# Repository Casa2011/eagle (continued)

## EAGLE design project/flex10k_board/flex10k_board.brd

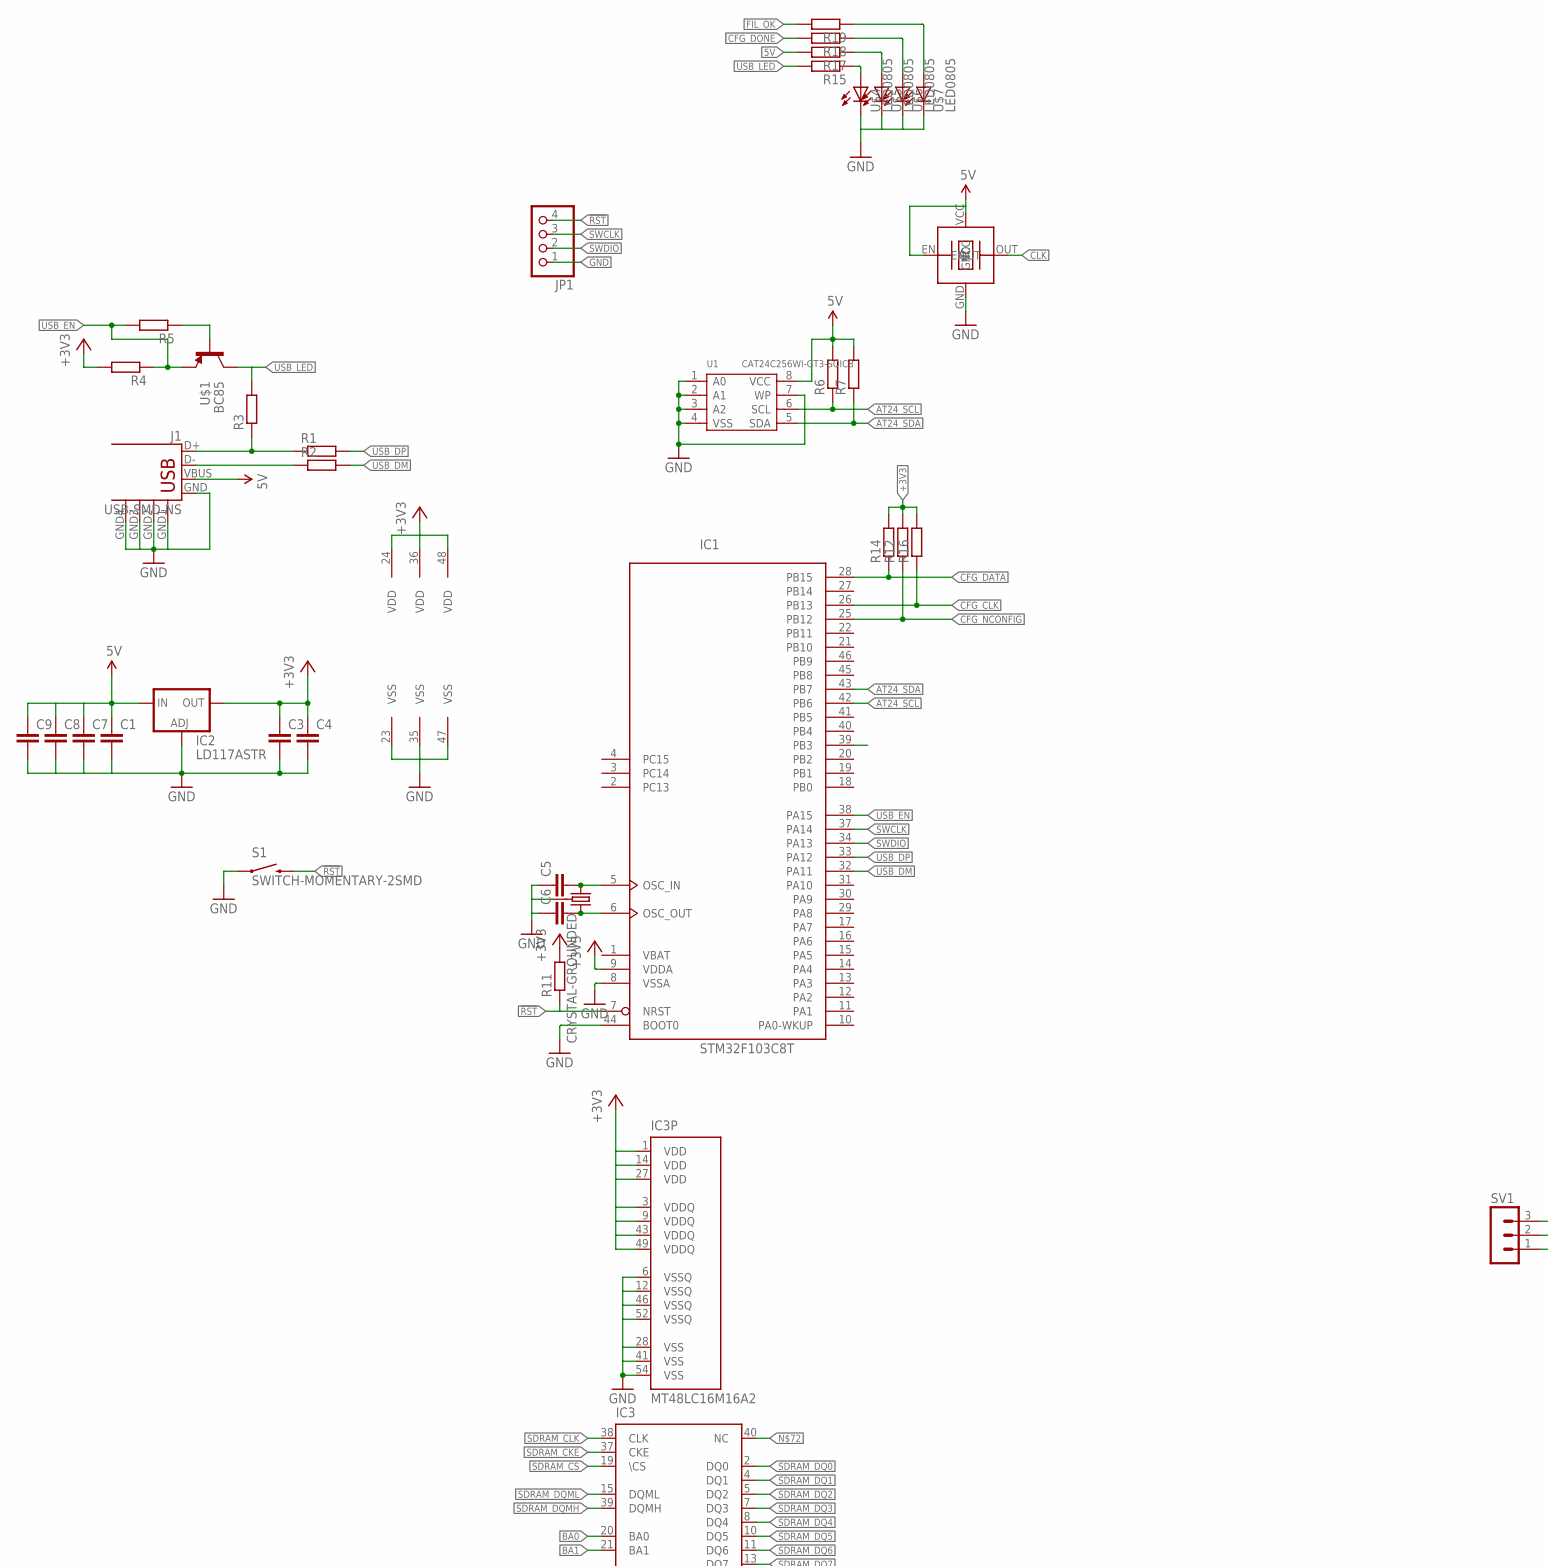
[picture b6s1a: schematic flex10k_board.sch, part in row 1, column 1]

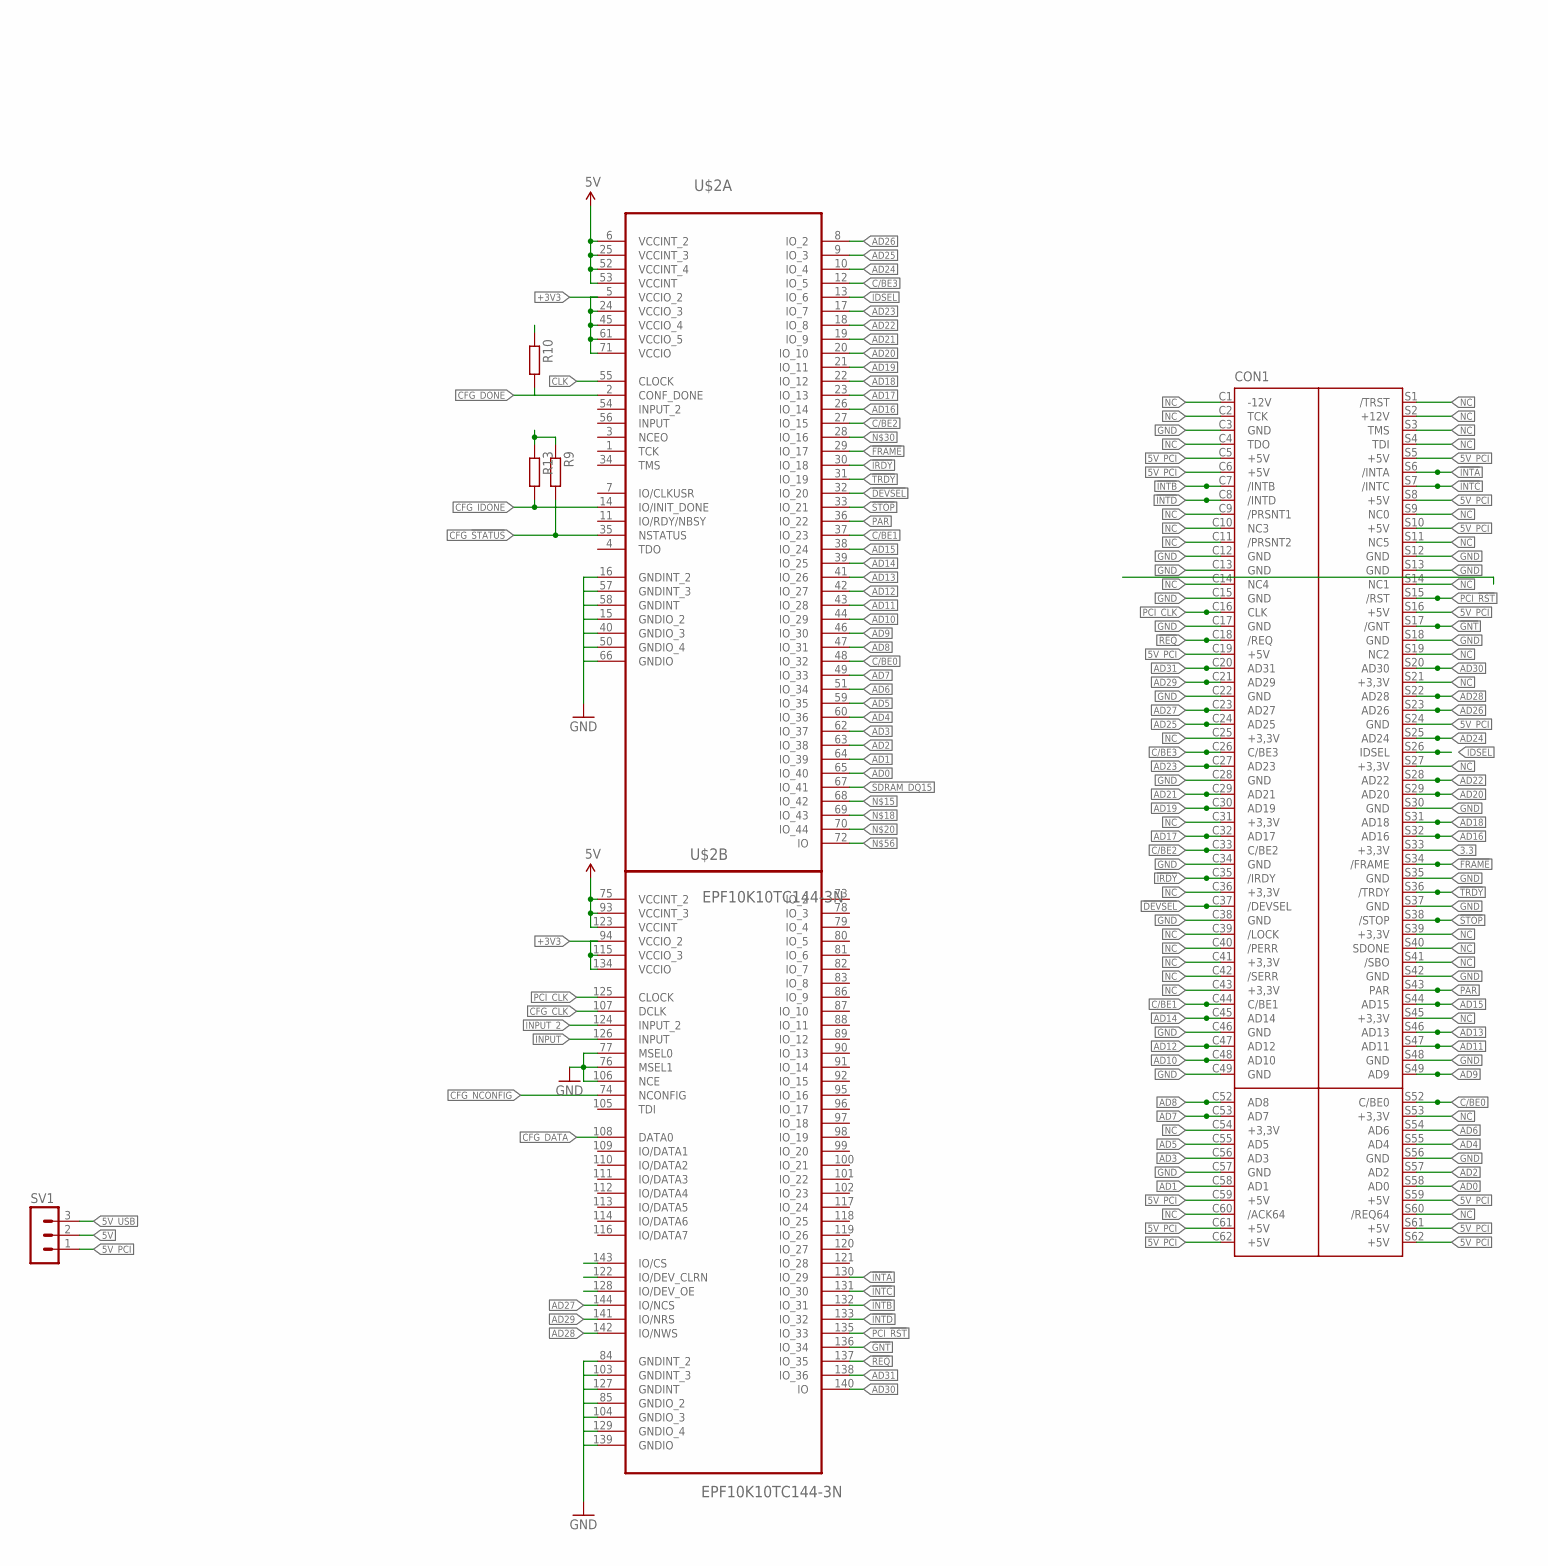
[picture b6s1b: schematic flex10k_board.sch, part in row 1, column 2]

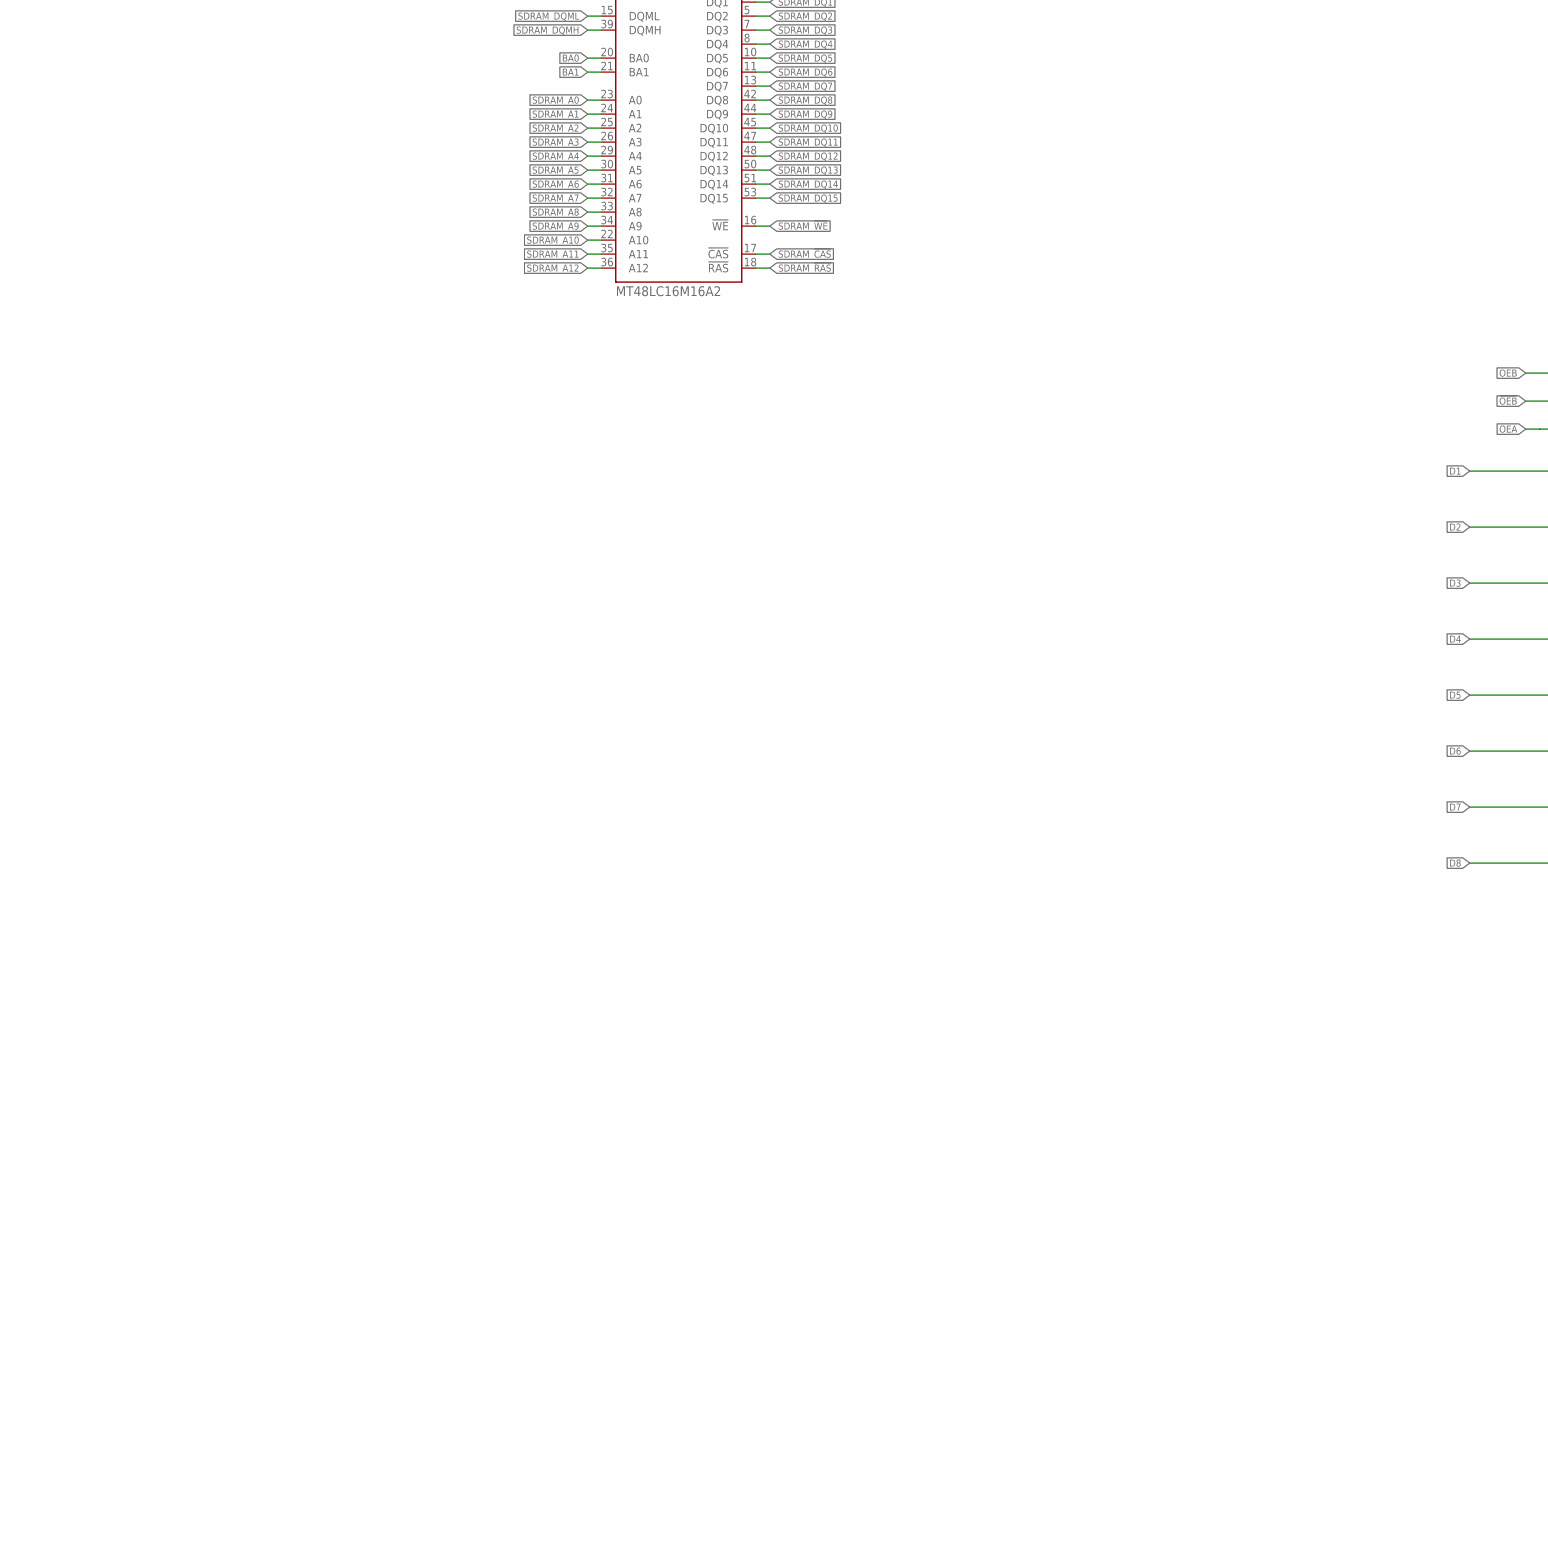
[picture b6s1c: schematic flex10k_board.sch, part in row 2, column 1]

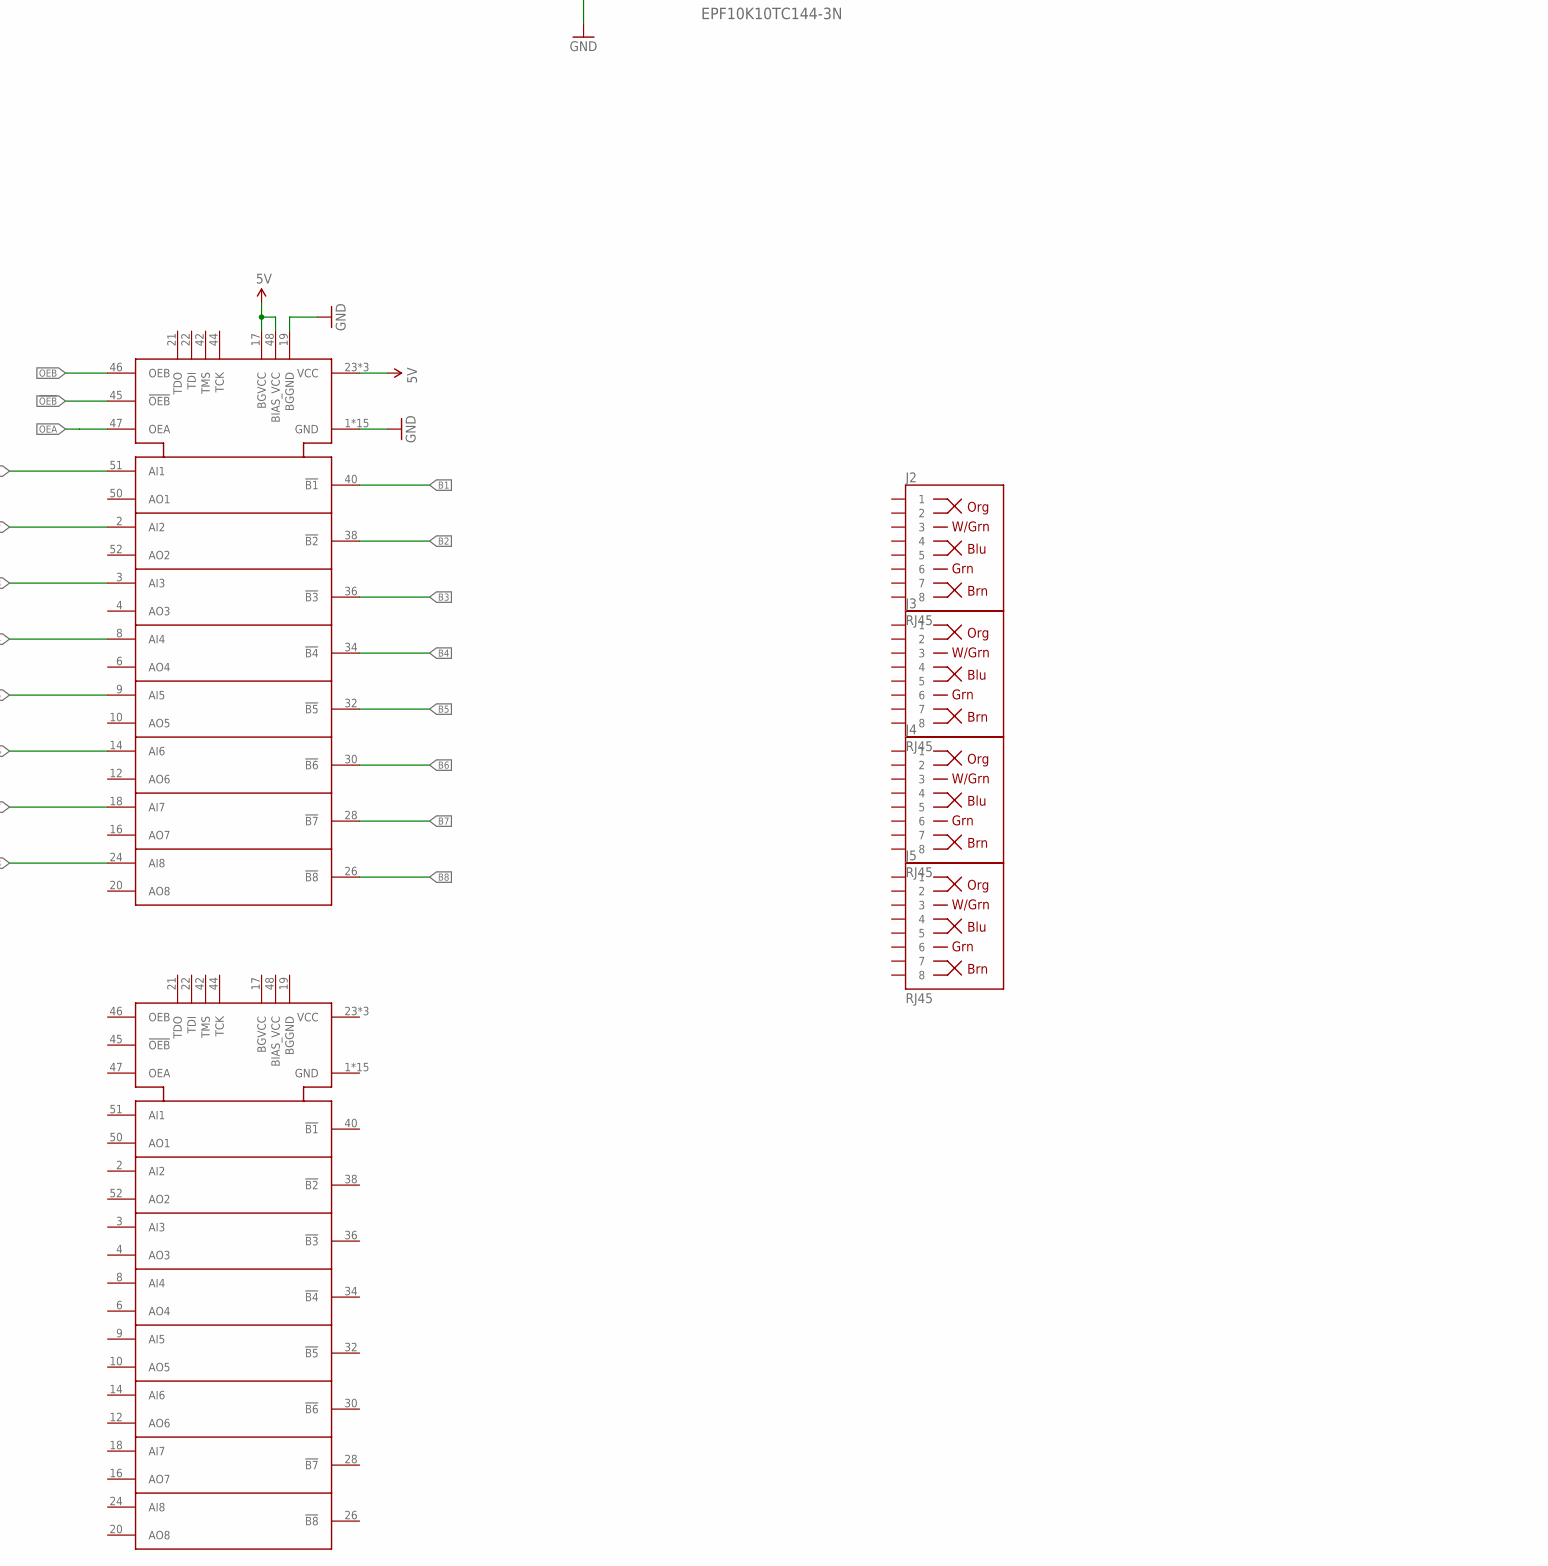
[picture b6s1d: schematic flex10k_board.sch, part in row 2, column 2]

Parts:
C1, C3, C4, C7, C8, C9: CC0805; C0805
C5, C6: CC0603; C0603
CON1: PCI_CON; PCI_BRDL
IC1: STM32F103C8T; LQFP48
IC2: LD117ASTR; SOT223
IC3: MT48LC16M16A2; TSOP54-400
J1: USB-SMD-NS; USB-MINIB-NOSTOP
J2, J3, J4, J5: RJ45; RJ45-8
JP1: PINHD-1X4; 1X04
R1, R2, R3, R4, R5, R6, R7, R9, R10, R11, R12, R13, R14, R15, R16, R17, R18, R19: R0603; 0603
S1: SWITCH-MOMENTARY-2SMD; TACTILE-SWITCH-SMD
SV1: MA03-1
U1: CAT24C256WI-GT3-SOIC8; SOIC8-1.27-5X4MM
U$1: BC85; SOT23
U$2: EPF10K10TC144-3N; QFP50P2200X2200X160-144N
U$3: TXC-BA; 7X5
U$4, U$5, U$6, U$7: LED0805; 0805-LED
U$8: CRYSTAL-GROUNDED; CRYSTAL-SMD-5X3
U$9, U$10: SN74FB2050; TQFP-10X10-52

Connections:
3.3: CON1.S33 (+3,3V)
5V: C1.1, C7.1, C8.1, C9.1, IC2.3 (IN), R6.2, R7.2, R17.2, SV1.2, U1.8 (VCC), U$2.6 (VCCINT_2), U$2.25 (VCCINT_3), U$2.52 (VCCINT_4), U$2.53 (VCCINT), U$2.75 (VCCINT_2), U$2.93 (VCCINT_3), U$2.123 (VCCINT), U$3.EN, U$3.VCC, U$10.17 (BGVCC), U$10.23 (VCC), U$10.43 (VCC), U$10.48 (BIAS_VCC), U$10.49 (VCC)
5V_PCI: CON1.C5 (+5V), CON1.C6 (+5V), CON1.C19 (+5V), CON1.C59 (+5V), CON1.C61 (+5V), CON1.C62 (+5V), CON1.S5 (+5V), CON1.S8 (+5V), CON1.S10 (+5V), CON1.S16 (+5V), CON1.S24 (GND), CON1.S59 (+5V), CON1.S61 (+5V), CON1.S62 (+5V), SV1.1
5V_USB: J1.VBUS, SV1.3
!DEVSEL: CON1.C37 (/DEVSEL), U$2.32 (IO_20)
!FRAME: CON1.S34 (/FRAME), U$2.29 (IO_17)
!GNT: CON1.S17 (/GNT), U$2.136 (IO_34)
!INTA: CON1.S6 (/INTA), U$2.130 (IO_29)
!INTB: CON1.C7 (/INTB), U$2.132 (IO_31)
!INTC: CON1.S7 (/INTC), U$2.131 (IO_30)
!INTD: CON1.C8 (/INTD), U$2.133 (IO_32)
!IRDY: CON1.C35 (/IRDY), U$2.30 (IO_18)
!OEB: U$10.45 (!OEB)
!REQ: CON1.C18 (/REQ), U$2.137 (IO_35)
!RST: IC1.7 (NRST), JP1.4, R11.1, S1.3 (2)
!STOP: CON1.S38 (/STOP), U$2.33 (IO_21)
!TRDY: CON1.S36 (/TRDY), U$2.31 (IO_19)
+3V3: C3.1, C4.1, IC1.9 (VDDA), IC1.24 (VDD), IC1.36 (VDD), IC1.48 (VDD), IC2.4 (OUT), IC3.1 (VDD), IC3.3 (VDDQ), IC3.9 (VDDQ), IC3.14 (VDD), IC3.27 (VDD), IC3.43 (VDDQ), IC3.49 (VDDQ), R4.2, R9.1, R10.1, R11.2, R12.2, R13.1, R14.2, R16.2, U$2.5 (VCCIO_2), U$2.24 (VCCIO_3), U$2.45 (VCCIO_4), U$2.61 (VCCIO_5), U$2.71 (VCCIO), U$2.94 (VCCIO_2), U$2.115 (VCCIO_3), U$2.134 (VCCIO)
AD0: CON1.S58 (AD0), U$2.65 (IO_40)
AD1: CON1.C58 (AD1), U$2.64 (IO_39)
AD2: CON1.S57 (AD2), U$2.63 (IO_38)
AD3: CON1.C56 (AD3), U$2.62 (IO_37)
AD4: CON1.S55 (AD4), U$2.60 (IO_36)
AD5: CON1.C55 (AD5), U$2.59 (IO_35)
AD6: CON1.S54 (AD6), U$2.51 (IO_34)
AD7: CON1.C53 (AD7), U$2.49 (IO_33)
AD8: CON1.C52 (AD8), U$2.47 (IO_31)
AD9: CON1.S49 (AD9), U$2.46 (IO_30)
AD10: CON1.C48 (AD10), U$2.44 (IO_29)
AD11: CON1.S47 (AD11), U$2.43 (IO_28)
AD12: CON1.C47 (AD12), U$2.42 (IO_27)
AD13: CON1.S46 (AD13), U$2.41 (IO_26)
AD14: CON1.C45 (AD14), U$2.39 (IO_25)
AD15: CON1.S44 (AD15), U$2.38 (IO_24)
AD16: CON1.S32 (AD16), U$2.26 (IO_14)
AD17: CON1.C32 (AD17), U$2.23 (IO_13)
AD18: CON1.S31 (AD18), U$2.22 (IO_12)
AD19: CON1.C30 (AD19), U$2.21 (IO_11)
AD20: CON1.S29 (AD20), U$2.20 (IO_10)
AD21: CON1.C29 (AD21), U$2.19 (IO_9)
AD22: CON1.S28 (AD22), U$2.18 (IO_8)
AD23: CON1.C27 (AD23), U$2.17 (IO_7)
AD24: CON1.S25 (AD24), U$2.10 (IO_4)
AD25: CON1.C24 (AD25), U$2.9 (IO_3)
AD26: CON1.S23 (AD26), U$2.8 (IO_2)
AD27: CON1.C23 (AD27), U$2.144 (IO/NCS)
AD28: CON1.S22 (AD28), U$2.142 (IO/NWS)
AD29: CON1.C21 (AD29), U$2.141 (IO/NRS)
AD30: CON1.S20 (AD30), U$2.140 (IO)
AD31: CON1.C20 (AD31), U$2.138 (IO_36)
AT24_SCL: IC1.42 (PB6), R6.1, U1.6 (SCL)
AT24_SDA: IC1.43 (PB7), R7.1, U1.5 (SDA)
B1: U$10.40 (!B1)
B2: U$10.38 (!B2)
B3: U$10.36 (!B3)
B4: U$10.34 (!B4)
B5: U$10.32 (!B5)
B6: U$10.30 (!B6)
B7: U$10.28 (!B7)
B8: U$10.26 (!B8)
BA0: IC3.20 (BA0)
BA1: IC3.21 (BA1)
C/BE0: CON1.S52 (C/BE0), U$2.48 (IO_32)
C/BE1: CON1.C44 (C/BE1), U$2.37 (IO_23)
C/BE2: CON1.C33 (C/BE2), U$2.27 (IO_15)
C/BE3: CON1.C26 (C/BE3), U$2.12 (IO_5)
CFG_!STATUS: R9.2, U$2.35 (NSTATUS)
CFG_CLK: IC1.26 (PB13), R16.1, U$2.107 (DCLK)
CFG_DATA: IC1.28 (PB15), R14.1, U$2.108 (DATA0)
CFG_DONE: R10.2, R18.2, U$2.2 (CONF_DONE)
CFG_IDONE: R13.2, U$2.14 (IO/INIT_DONE)
CFG_NCONFIG: IC1.25 (PB12), R12.1, U$2.74 (NCONFIG)
CLK: U$2.55 (CLOCK), U$3.OUT
D1: U$10.51 (AI1)
D2: U$10.2 (AI2)
D3: U$10.3 (AI3)
D4: U$10.8 (AI4)
D5: U$10.9 (AI5)
D6: U$10.14 (AI6)
D7: U$10.18 (AI7)
D8: U$10.24 (AI8)
FIL_OK: IC1.39 (PB3), R19.2
GND: C1.2, C3.2, C4.2, C5.1, C6.1, C7.2, C8.2, C9.2, CON1.C3 (GND), CON1.C12 (GND), CON1.C13 (GND), CON1.C15 (GND), CON1.C17 (GND), CON1.C22 (GND), CON1.C28 (GND), CON1.C34 (GND), CON1.C38 (GND), CON1.C46 (GND), CON1.C49 (GND), CON1.C57 (GND), CON1.S12 (GND), CON1.S13 (GND), CON1.S18 (GND), CON1.S30 (GND), CON1.S35 (GND), CON1.S37 (GND), CON1.S42 (GND), CON1.S48 (GND), CON1.S56 (GND), IC1.8 (VSSA), IC1.23 (VSS), IC1.35 (VSS), IC1.44 (BOOT0), IC1.47 (VSS), IC2.1 (ADJ), IC3.6 (VSSQ), IC3.12 (VSSQ), IC3.28 (VSS), IC3.41 (VSS), IC3.46 (VSSQ), IC3.52 (VSSQ), IC3.54 (VSS), J1.GND, J1.GND1 (GND), J1.GND2 (GND), J1.GND3 (GND), J1.GND4 (GND), JP1.1, S1.1, U1.1 (A0), U1.2 (A1), U1.3 (A2), U1.4 (VSS), U1.7 (WP), U$2.15 (GNDIO_2), U$2.16 (GNDINT_2), U$2.40 (GNDIO_3), U$2.50 (GNDIO_4), U$2.57 (GNDINT_3), U$2.58 (GNDINT), U$2.66 (GNDIO), U$2.76 (MSEL1), U$2.77 (MSEL0), U$2.84 (GNDINT_2), U$2.85 (GNDIO_2), U$2.103 (GNDINT_3), U$2.104 (GNDIO_3), U$2.106 (NCE), U$2.127 (GNDINT), U$2.129 (GNDIO_4), U$2.139 (GNDIO), U$3.GND, U$4.C, U$5.C, U$6.C, U$7.C, U$8.2 (3), U$8.4 (3), U$10.1 (GND), U$10.5 (GND), U$10.7 (GND), U$10.11 (GND), U$10.13 (GND), U$10.15 (GND), U$10.19 (BGGND), U$10.25 (GND), U$10.27 (GND), U$10.29 (GND), U$10.31 (GND), U$10.33 (GND), U$10.35 (GND), U$10.37 (GND), U$10.39 (GND), U$10.41 (GND)
IDSEL: CON1.S26 (IDSEL), U$2.13 (IO_6)
INPUT: U$2.126 (INPUT)
INPUT_2: U$2.124 (INPUT_2)
unnamed: C5.2, IC1.5 (OSC_IN), U$8.3 (1)
unnamed: J1.D-, R2.1
unnamed: C6.2, IC1.6 (OSC_OUT), U$8.1 (2)
unnamed: J1.D+, R1.1, R3.1
unnamed: R5.1, U$1.1 (B)
unnamed: R15.1, U$4.A
unnamed: R17.1, U$5.A
unnamed: R18.1, U$6.A
unnamed: R19.1, U$7.A
NC: CON1.C1 (-12V), CON1.C2 (TCK), CON1.C4 (TDO), CON1.C9 (/PRSNT1), CON1.C10 (NC3), CON1.C11 (/PRSNT2), CON1.C14 (NC4), CON1.C25 (+3,3V), CON1.C31 (+3,3V), CON1.C36 (+3,3V), CON1.C39 (/LOCK), CON1.C40 (/PERR), CON1.C41 (+3,3V), CON1.C42 (/SERR), CON1.C43 (+3,3V), CON1.C54 (+3,3V), CON1.C60 (/ACK64), CON1.S1 (/TRST), CON1.S2 (+12V), CON1.S3 (TMS), CON1.S4 (TDI), CON1.S9 (NC0), CON1.S11 (NC5), CON1.S14 (NC1), CON1.S19 (NC2), CON1.S21 (+3,3V), CON1.S27 (+3,3V), CON1.S39 (+3,3V), CON1.S40 (SDONE), CON1.S41 (/SBO), CON1.S45 (+3,3V), CON1.S53 (+3,3V), CON1.S60 (/REQ64)
OEA: U$10.47 (OEA)
OEB: U$10.46 (OEB)
PAR: CON1.S43 (PAR), U$2.36 (IO_22)
PCI_!RST: CON1.S15 (/RST), U$2.135 (IO_33)
PCI_CLK: CON1.C16 (CLK), U$2.125 (CLOCK)
SDRAM_!CAS: IC3.17 (!CAS)
SDRAM_!RAS: IC3.18 (!RAS)
SDRAM_!WE: IC3.16 (!WE)
SDRAM_A0: IC3.23 (A0)
SDRAM_A1: IC3.24 (A1)
SDRAM_A2: IC3.25 (A2)
SDRAM_A3: IC3.26 (A3)
SDRAM_A4: IC3.29 (A4)
SDRAM_A5: IC3.30 (A5)
SDRAM_A6: IC3.31 (A6)
SDRAM_A7: IC3.32 (A7)
SDRAM_A8: IC3.33 (A8)
SDRAM_A9: IC3.34 (A9)
SDRAM_A10: IC3.22 (A10)
SDRAM_A11: IC3.35 (A11)
SDRAM_A12: IC3.36 (A12)
SDRAM_CKE: IC3.37 (CKE)
SDRAM_CLK: IC3.38 (CLK)
SDRAM_CS: IC3.19 (\CS)
SDRAM_DQ0: IC3.2 (DQ0)
SDRAM_DQ1: IC3.4 (DQ1)
SDRAM_DQ2: IC3.5 (DQ2)
SDRAM_DQ3: IC3.7 (DQ3)
SDRAM_DQ4: IC3.8 (DQ4)
SDRAM_DQ5: IC3.10 (DQ5)
SDRAM_DQ6: IC3.11 (DQ6)
SDRAM_DQ7: IC3.13 (DQ7)
SDRAM_DQ8: IC3.42 (DQ8)
SDRAM_DQ9: IC3.44 (DQ9)
SDRAM_DQ10: IC3.45 (DQ10)
SDRAM_DQ11: IC3.47 (DQ11)
SDRAM_DQ12: IC3.48 (DQ12)
SDRAM_DQ13: IC3.50 (DQ13)
SDRAM_DQ14: IC3.51 (DQ14)
SDRAM_DQ15: IC3.53 (DQ15), U$2.67 (IO_41)
SDRAM_DQMH: IC3.39 (DQMH)
SDRAM_DQML: IC3.15 (DQML)
SWCLK: IC1.37 (PA14), JP1.3
SWDIO: IC1.34 (PA13), JP1.2
USB_DM: IC1.32 (PA11), R2.2
USB_DP: IC1.33 (PA12), R1.2
USB_EN: IC1.38 (PA15), R4.1, R5.2, U$1.2 (E)
USB_LED: R3.2, R15.2, U$1.3 (C)
VBAT: IC1.1 (VBAT)

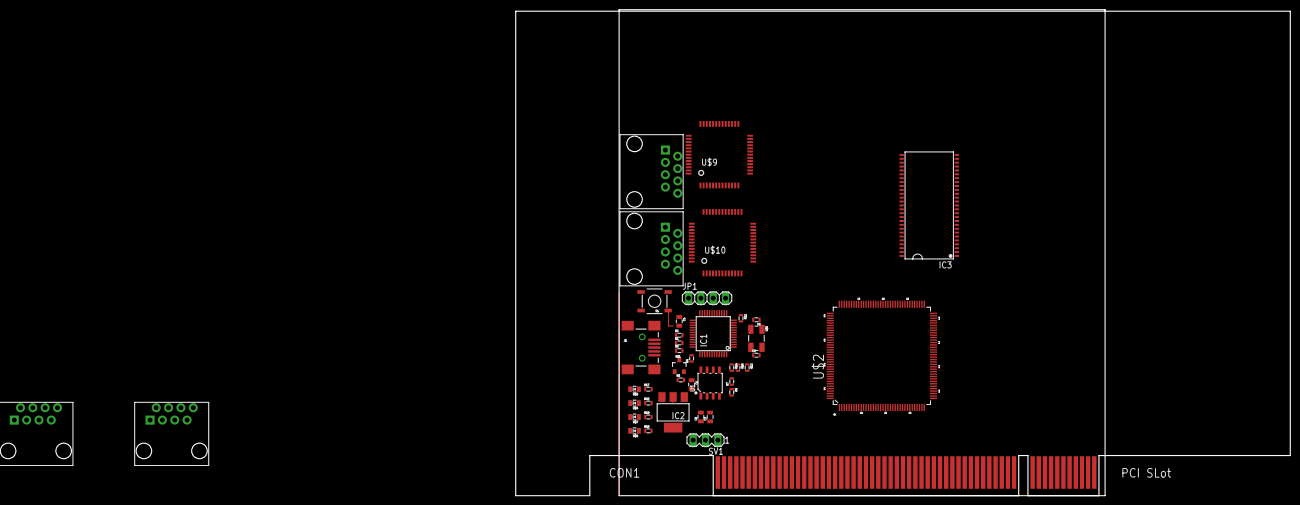
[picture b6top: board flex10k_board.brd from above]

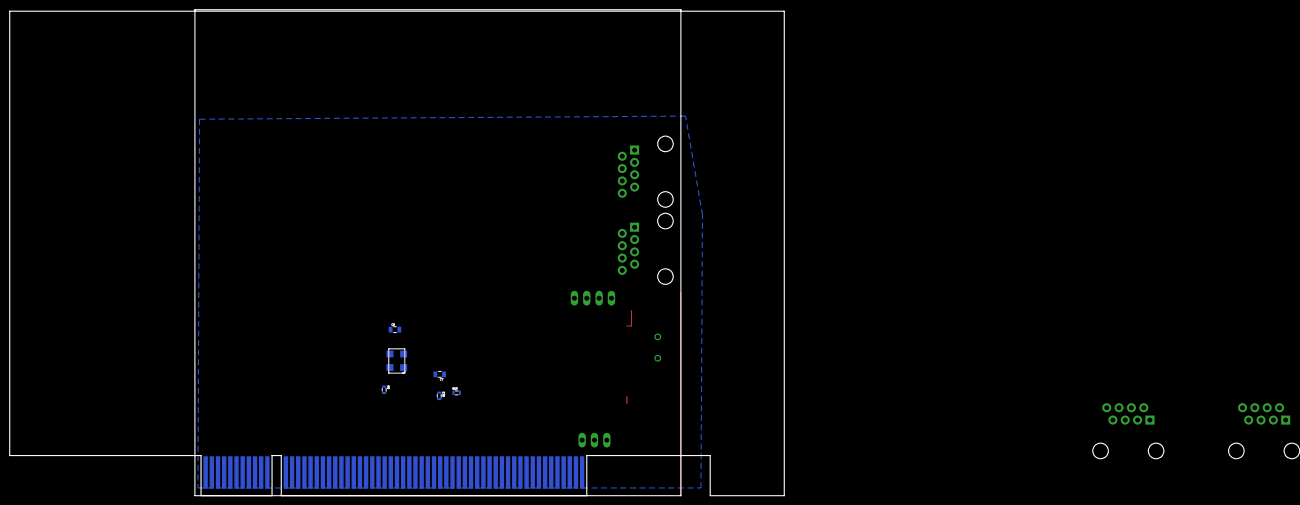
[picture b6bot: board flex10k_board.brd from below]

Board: 2 copper layers, 159.4 x 99.7 mm, 49 parts (6 on the bottom side), 84 nets.

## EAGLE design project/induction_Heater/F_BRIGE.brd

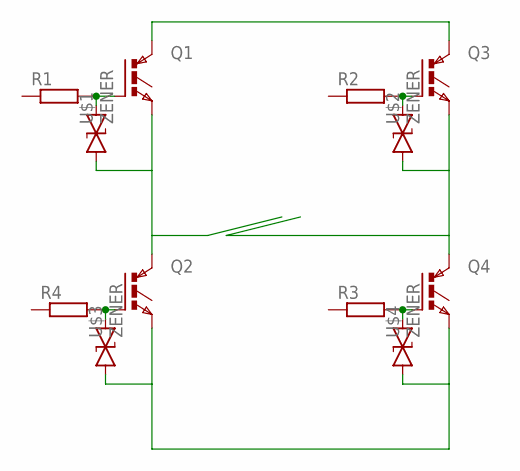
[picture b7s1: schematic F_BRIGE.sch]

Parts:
Q1, Q2, Q3, Q4: IGBTTO247H; TO247BH
R1, R2, R3, R4: R-EU_0414/5V; 0414V
U$1, U$2, U$3, U$4: ZENER; SMA-DIODE

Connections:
GND: Q2.S (E), Q4.S (E), U$3.A, U$4.A
unnamed: Q1.G, R1.2, U$1.C
unnamed: Q3.G, R2.2, U$2.C
unnamed: Q2.G, R4.2, U$3.C
unnamed: Q4.G, R3.2, U$4.C
OUT1: Q1.S (E), Q2.D (C), U$1.A
OUT2: Q3.S (E), Q4.D (C), U$2.A
VCC: Q1.D (C), Q3.D (C)

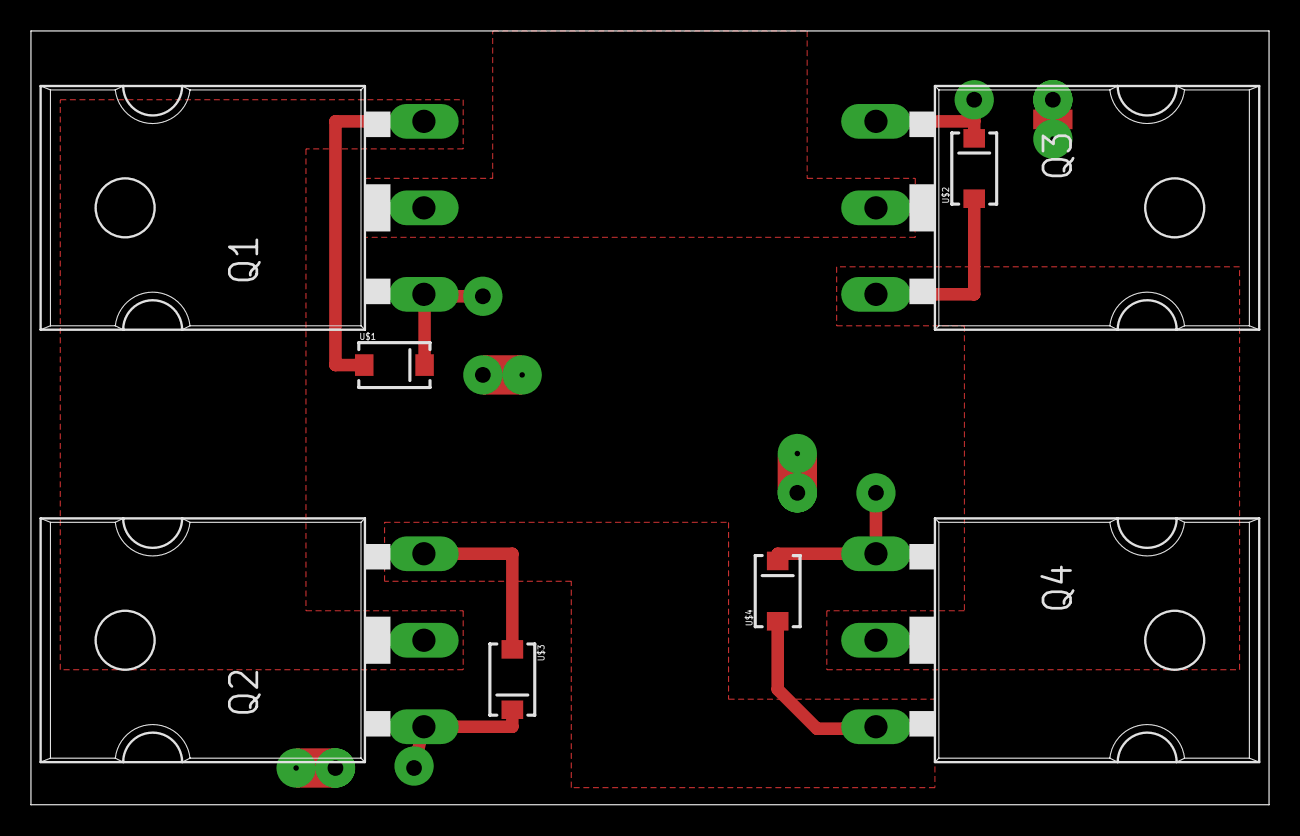
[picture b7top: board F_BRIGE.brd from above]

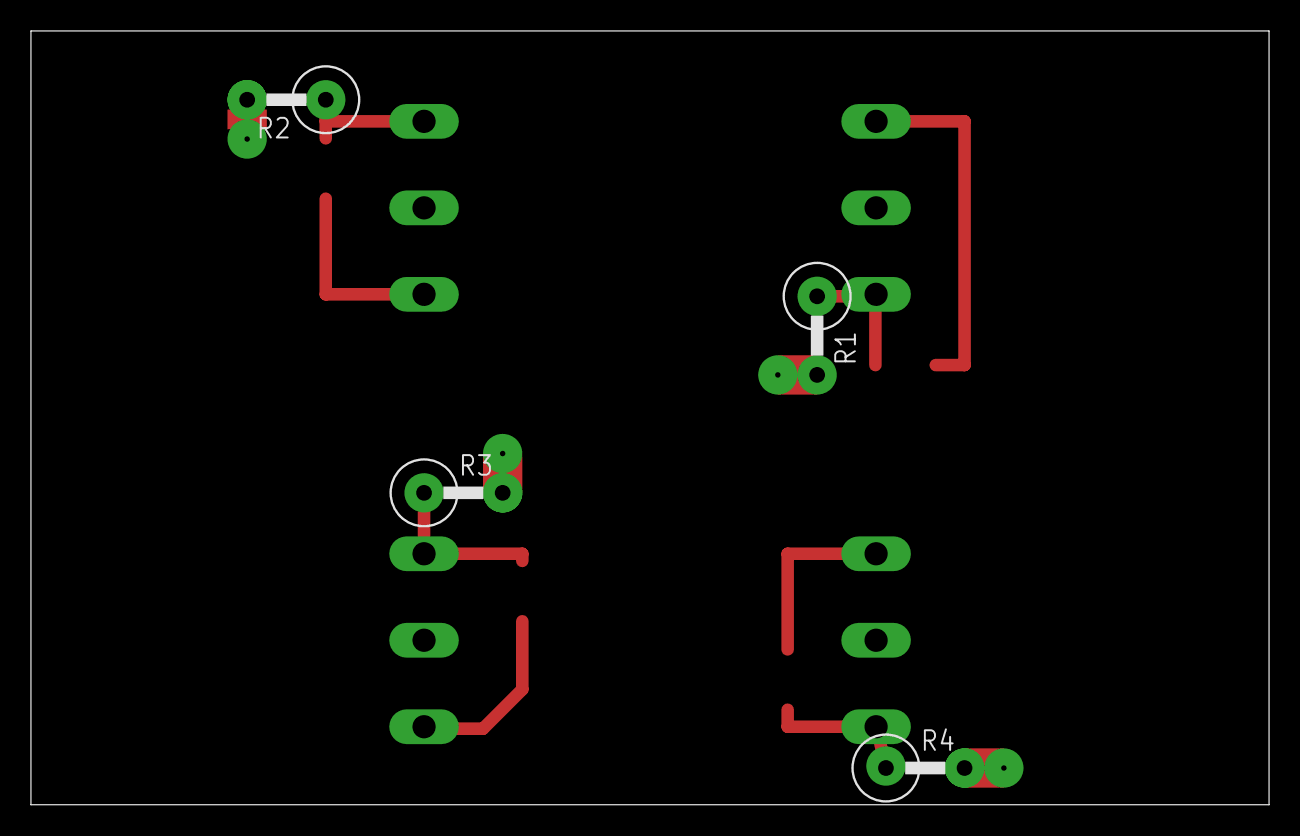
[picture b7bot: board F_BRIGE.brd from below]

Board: 2 copper layers, 80.0 x 50.0 mm, 12 parts (4 on the bottom side), 8 nets.
